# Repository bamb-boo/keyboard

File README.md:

# bamb-boo's mechanical keyboard!

This is a custom wired mechanical keyboard using a raspberry pi pico and really nice switches!! The keyboard also has a _negative_ tilt, which is better for your wrists (carpal tunnel syndrome). It uses a 16x6 matrix and has 83 keys, which is the best for my personal preference! 

It can act as an alternative to other popular keyboards like the Aula F75 or similar keyboards due to its more ergonomic and hand-friendly design!

### Features!

- Has 83 keys (~75% keyboard)

- Non-hotswappable Click Inc HP Switches (hotswappable will increase cost and design time, so kept it simple ;] )

- Runs on a Raspberry Pi Pico due to its powerful chip and the number of IO pins (26 pins)

- Has a 16x6 matrix, which is all I need for my needs (_not_ an aspiring accountant, though it'll be cool to have a larger keyboard)

- 1N4148 through-hole diodes to prevent ghosting (The matrix is a useful way of succinctly employing a limited number of IO pins for a large number of keys)

### Why I made it

To be honest, I had a faulty laptop keyboard, and wanted to get a mechanical keyboard. Creating my own keyboard >>> buying a pre-made one, so I just decided to make one on a whim! ✨

### Future scope-

I would REALLY love to make a-

- A keyboard using a touchscreen to for more efficiency (and fun, who doesn't like repeating GIFs)
- Wireless version using Pi Pico W (because you can't always stay connected to your laptop!)
- Make a larger keyboard (because larger is always equal to better!)

### Photos-

(looks kinda wonky because my laptop became incredibly slow, and it was trouble to get anything done let alone model in fusion 360.)

(just case)

(case+pcb)

(pcb)

(schematic)

### Build instructions-

1. Solder the diodes to the designated holes in the pcb, with the diodes pointing down.

2. Solder the pi pico using headers onto the pcb

3. Flash the firmware-
    plug in the usb and connect it to a laptop.
    Drop the .uf2 file 

4. Use [https://www.keyboardtester.com/tester.html](https://www.keyboardtester.com/tester.html) to test if all connections are correct- this mitigates the need to annoyingly verify if all connections are right later on

5. Solder the switches to the holes beside the diodes.

6. Clip the stabilizers onto the pcb.

7. Attach the keycaps to the switches.

8. Attach the pcb to the plate, ensuring the fit snugly.

9. Bolt the plate to the case using the screws.

10. Viola, you're done!

Finally, I heartfully thank PCBWay for their sponsorship, which allowed me to experiment and become a creator. Their quality is very high and they offer a wide range of helpful services such as PCB manufacturing, 3D-printing and CNC machining. Visit PCBWay at [PCBWay](https://www.pcbway.com)

[Bill of Materials](https://github.com/bamb-boo/keyboard/blob/main/cart/README.md) (refer to the hyperlink for the detailed bom present in the cart directory)-
| Component name    | Qty        | Bought from | Cost (usd) |
|-------------------|------------|-----------------------------------------------------------------------------------------------------------------------------------------------------------------------------------------------------------------------------------------------------------------------|------------|
| Case              | 1          | pcbway| 50       |
| Plate             |  1          | pcbway| 30       |
|PCB                | 1          | pcbway| 30         |
| Switches          | 9 packs    | [link](https://stackskb.com/store/click-inc-hp-switch-pack-of-10-pre-order/)| 17         |
| Keycaps           | 83 keycaps | [link](https://meckeys.com/shop/accessories/keyboard-accessories/keycaps/colour-pbt-keycaps/)| about 11   |
| M2 nuts and bolts | 8          | Local vendor| 1          |
| Raspbeery pi pico | 1          | [link](https://quartzcomponents.com/products/raspberry-pi-pico?variant=37945289801912&country=IN&currency=INR&utm_medium=product_sync&utm_source=google&utm_content=sag_organic&utm_campaign=sag_organic&srsltid=AfmBOooph4yAOKlaXOlzuqV4wVWYXD59shyxalMg0NoKKp0ef7S1frVsyPs) | 3.5        |
| Stabilizers       | 5          | [link](https://www.genesispc.in/products/durock-plate-mount-stabilizers-6-25u-4x2u-black?variant=43129560924213)| 4          |
| Diodes            |83         | [link](https://www.ktron.in/product/diode-1n4148-th/?srsltid=AfmBOoqAQ2ie58oqGB9lnuLERS_E0bK5uivKzd28IHgtJRiMNgbBmKTvdes)| 0.6        |
|Total              |           |                 |148  |

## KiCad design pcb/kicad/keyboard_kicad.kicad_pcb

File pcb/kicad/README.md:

This folder contains the kicad files for the PCB.

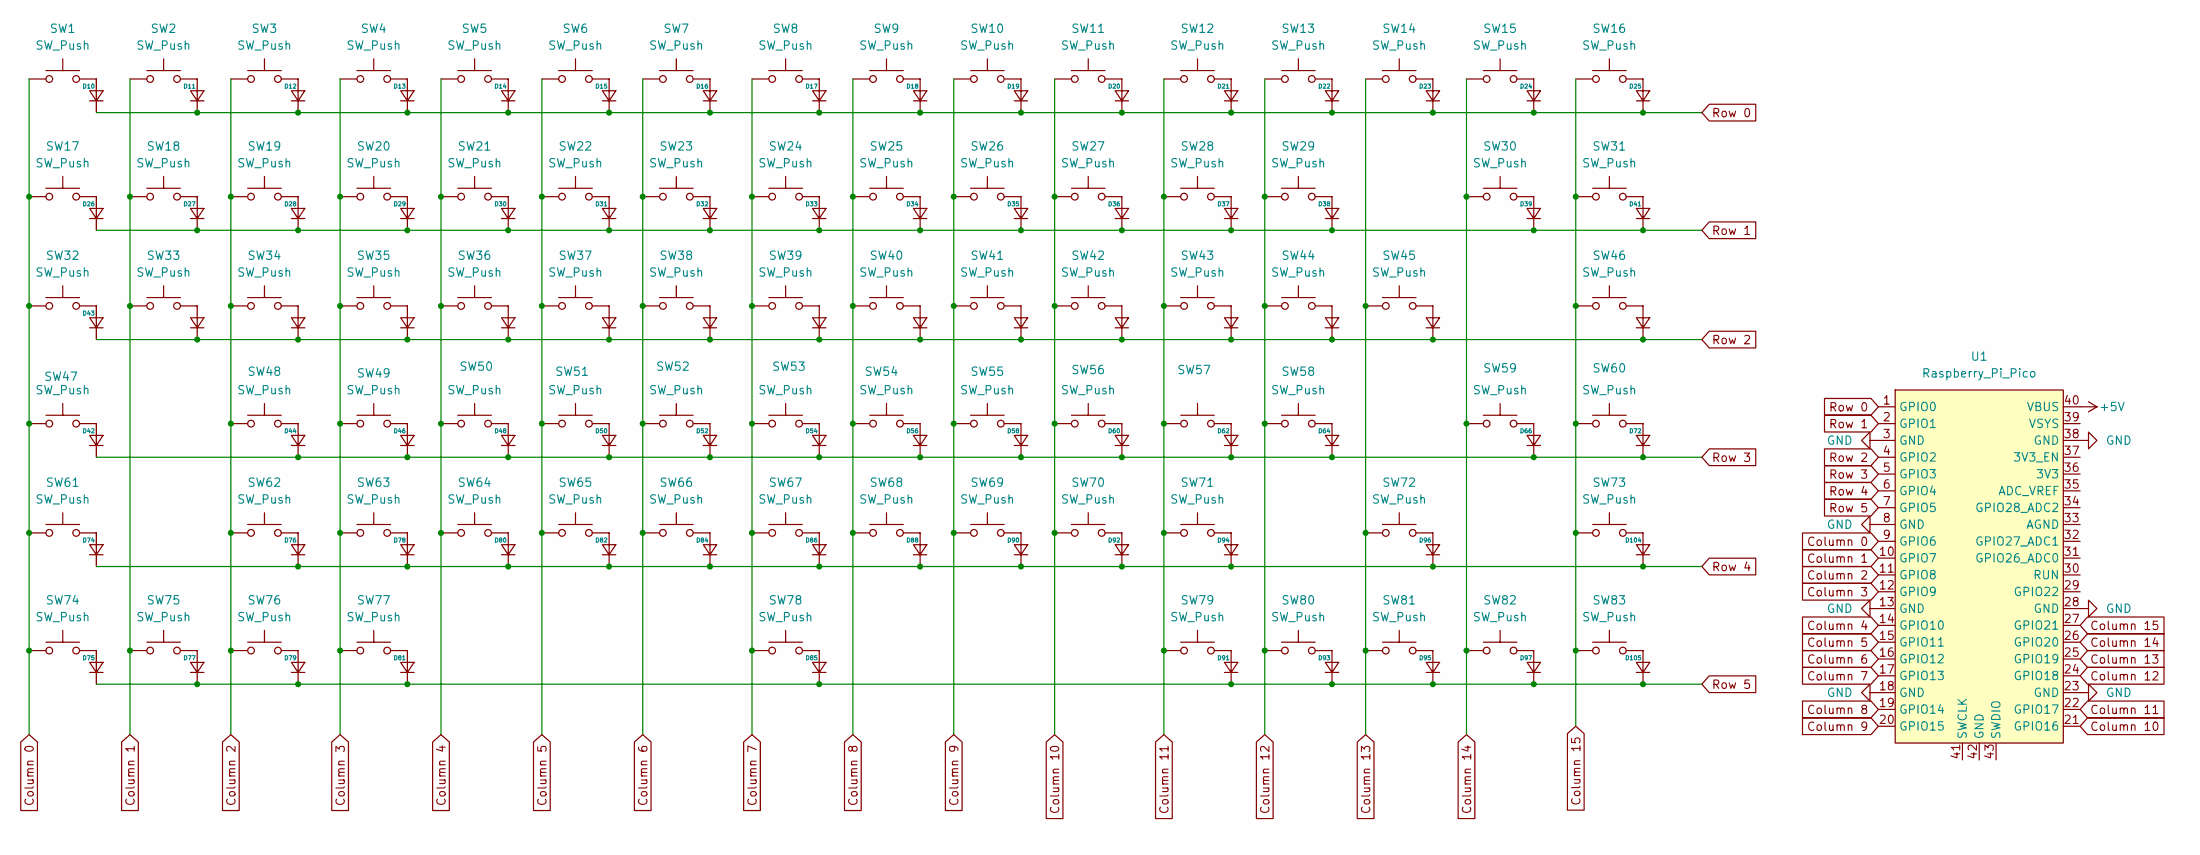
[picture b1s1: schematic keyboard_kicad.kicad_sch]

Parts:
D10, D11, D12, D13, D14, D15, D16, D17, D18, D19, D20, D21, D22, D23, D24, D25, D26, D27, D28, D29, D30, D31, D32, D33, D34, D35, D36, D37, D38, D39, D41, D42, D43, D44, D45, D46, D47, D48, D49, D50, D51, D52, D53, D54, D55, D56, D57, D58, D59, D60, D61, D62, D63, D64, D65, D66, D67, D69, D72, D73, D74, D75, D76, D77, D78, D79, D80, D81, D82, D84, D85, D86, D88, D90, D91, D92, D93, D94, D95, D96, D97, D104, D105: D_DO-35_SOD27_P3.81mm_Vertical_KathodeUp
SW1, SW2, SW3, SW4, SW5, SW6, SW7, SW8, SW9, SW10, SW11, SW12, SW13, SW14, SW15, SW16, SW17, SW18, SW19, SW20, SW21, SW22, SW23, SW24, SW25, SW26, SW27, SW28, SW29, SW31, SW33, SW34, SW35, SW36, SW37, SW38, SW39, SW40, SW41, SW42, SW43, SW44, SW46, SW48, SW49, SW50, SW51, SW52, SW53, SW54, SW55, SW56, SW57, SW58, SW60, SW62, SW63, SW64, SW65, SW66, SW67, SW68, SW69, SW70, SW71, SW73, SW79, SW80, SW81, SW82, SW83: SW_Push; MX_PCB_1.00u
SW30: SW_Push; MX_PCB_2.00u
SW32, SW45: SW_Push; MX_PCB_1.50u
SW47: SW_Push; MX_PCB_1.75u
SW59, SW61: SW_Push; MX_PCB_2.25u
SW72: SW_Push; MX_PCB_2.75u
SW74, SW75, SW76, SW77: SW_Push; MX_PCB_1.25u
SW78: SW_Push; Stabilizer_Cherry_MX_6.25u
U1: Raspberry_Pi_Pico

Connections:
+5V: U1.40 (VBUS)
Column 0: SW1.1, SW17.1, SW32.1, SW47.1, SW61.1, SW74.1, U1.9 (GPIO6)
Column 1: SW2.1, SW18.1, SW33.1, SW75.1, U1.10 (GPIO7)
Column 2: SW3.1, SW19.1, SW34.1, SW48.1, SW62.1, SW76.1, U1.11 (GPIO8)
Column 3: SW4.1, SW20.1, SW35.1, SW49.1, SW63.1, SW77.1, U1.12 (GPIO9)
Column 4: SW5.1, SW21.1, SW36.1, SW50.1, SW64.1, U1.14 (GPIO10)
Column 5: SW6.1, SW22.1, SW37.1, SW51.1, SW65.1, U1.15 (GPIO11)
Column 6: SW7.1, SW23.1, SW38.1, SW52.1, SW66.1, U1.16 (GPIO12)
Column 7: SW8.1, SW24.1, SW39.1, SW53.1, SW67.1, SW78.1, U1.17 (GPIO13)
Column 8: SW9.1, SW25.1, SW40.1, SW54.1, SW68.1, U1.19 (GPIO14)
Column 9: SW10.1, SW26.1, SW41.1, SW55.1, SW69.1, U1.20 (GPIO15)
Column 10: SW11.1, SW27.1, SW42.1, SW56.1, SW70.1, U1.21 (GPIO16)
Column 11: SW12.1, SW28.1, SW43.1, SW57.1, SW71.1, SW79.1, U1.22 (GPIO17)
Column 12: SW13.1, SW29.1, SW44.1, SW58.1, SW80.1, U1.24 (GPIO18)
Column 13: SW14.1, SW45.1, SW72.1, SW81.1, U1.25 (GPIO19)
Column 14: SW15.1, SW30.1, SW59.1, SW82.1, U1.26 (GPIO20)
Column 15: SW16.1, SW31.1, SW46.1, SW60.1, SW73.1, SW83.1, U1.27 (GPIO21)
GND: U1.3 (GND), U1.8 (GND), U1.13 (GND), U1.18 (GND), U1.23 (GND), U1.28 (GND), U1.38 (GND)
unnamed: D10.2 (A), SW1.2
unnamed: D11.2 (A), SW2.2
unnamed: D12.2 (A), SW3.2
unnamed: D13.2 (A), SW4.2
unnamed: D14.2 (A), SW5.2
unnamed: D15.2 (A), SW6.2
unnamed: D16.2 (A), SW7.2
unnamed: D17.2 (A), SW8.2
unnamed: D18.2 (A), SW9.2
unnamed: D19.2 (A), SW10.2
unnamed: D20.2 (A), SW11.2
unnamed: D21.2 (A), SW12.2
unnamed: D22.2 (A), SW13.2
unnamed: D23.2 (A), SW14.2
unnamed: D24.2 (A), SW15.2
unnamed: D25.2 (A), SW16.2
unnamed: D26.2 (A), SW17.2
unnamed: D27.2 (A), SW18.2
unnamed: D28.2 (A), SW19.2
unnamed: D29.2 (A), SW20.2
unnamed: D30.2 (A), SW21.2
unnamed: D31.2 (A), SW22.2
unnamed: D32.2 (A), SW23.2
unnamed: D33.2 (A), SW24.2
unnamed: D34.2 (A), SW25.2
unnamed: D35.2 (A), SW26.2
unnamed: D36.2 (A), SW27.2
unnamed: D37.2 (A), SW28.2
unnamed: D38.2 (A), SW29.2
unnamed: D39.2 (A), SW30.2
unnamed: D41.2 (A), SW31.2
unnamed: D42.2 (A), SW47.2
unnamed: D43.2 (A), SW32.2
unnamed: D44.2 (A), SW48.2
unnamed: D45.2 (A), SW33.2
unnamed: D46.2 (A), SW49.2
unnamed: D47.2 (A), SW34.2
unnamed: D48.2 (A), SW50.2
unnamed: D49.2 (A), SW35.2
unnamed: D50.2 (A), SW51.2
unnamed: D51.2 (A), SW36.2
unnamed: D52.2 (A), SW52.2
unnamed: D53.2 (A), SW37.2
unnamed: D54.2 (A), SW53.2
unnamed: D55.2 (A), SW38.2
unnamed: D56.2 (A), SW54.2
unnamed: D57.2 (A), SW39.2
unnamed: D58.2 (A), SW55.2
unnamed: D59.2 (A), SW40.2
unnamed: D60.2 (A), SW56.2
unnamed: D61.2 (A), SW41.2
unnamed: D62.2 (A), SW57.2
unnamed: D63.2 (A), SW42.2
unnamed: D64.2 (A), SW58.2
unnamed: D65.2 (A), SW43.2
unnamed: D66.2 (A), SW59.2
unnamed: D67.2 (A), SW44.2
unnamed: D69.2 (A), SW45.2
unnamed: D72.2 (A), SW60.2
unnamed: D73.2 (A), SW46.2
unnamed: D74.2 (A), SW61.2
unnamed: D75.2 (A), SW74.2
unnamed: D76.2 (A), SW62.2
unnamed: D77.2 (A), SW75.2
unnamed: D78.2 (A), SW63.2
unnamed: D79.2 (A), SW76.2
unnamed: D80.2 (A), SW64.2
unnamed: D81.2 (A), SW77.2
unnamed: D82.2 (A), SW65.2
unnamed: D84.2 (A), SW66.2
unnamed: D85.2 (A), SW78.2
unnamed: D86.2 (A), SW67.2
unnamed: D88.2 (A), SW68.2
unnamed: D90.2 (A), SW69.2
unnamed: D91.2 (A), SW79.2
unnamed: D92.2 (A), SW70.2
unnamed: D93.2 (A), SW80.2
unnamed: D94.2 (A), SW71.2
unnamed: D95.2 (A), SW81.2
unnamed: D96.2 (A), SW72.2
unnamed: D97.2 (A), SW82.2
unnamed: D104.2 (A), SW73.2
unnamed: D105.2 (A), SW83.2
Row 0: D10.1 (K), D11.1 (K), D12.1 (K), D13.1 (K), D14.1 (K), D15.1 (K), D16.1 (K), D17.1 (K), D18.1 (K), D19.1 (K), D20.1 (K), D21.1 (K), D22.1 (K), D23.1 (K), D24.1 (K), D25.1 (K), U1.1 (GPIO0)
Row 1: D26.1 (K), D27.1 (K), D28.1 (K), D29.1 (K), D30.1 (K), D31.1 (K), D32.1 (K), D33.1 (K), D34.1 (K), D35.1 (K), D36.1 (K), D37.1 (K), D38.1 (K), D39.1 (K), D41.1 (K), U1.2 (GPIO1)
Row 2: D43.1 (K), D45.1 (K), D47.1 (K), D49.1 (K), D51.1 (K), D53.1 (K), D55.1 (K), D57.1 (K), D59.1 (K), D61.1 (K), D63.1 (K), D65.1 (K), D67.1 (K), D69.1 (K), D73.1 (K), U1.4 (GPIO2)
Row 3: D42.1 (K), D44.1 (K), D46.1 (K), D48.1 (K), D50.1 (K), D52.1 (K), D54.1 (K), D56.1 (K), D58.1 (K), D60.1 (K), D62.1 (K), D64.1 (K), D66.1 (K), D72.1 (K), U1.5 (GPIO3)
Row 4: D74.1 (K), D76.1 (K), D78.1 (K), D80.1 (K), D82.1 (K), D84.1 (K), D86.1 (K), D88.1 (K), D90.1 (K), D92.1 (K), D94.1 (K), D96.1 (K), D104.1 (K), U1.6 (GPIO4)
Row 5: D75.1 (K), D77.1 (K), D79.1 (K), D81.1 (K), D85.1 (K), D91.1 (K), D93.1 (K), D95.1 (K), D97.1 (K), D105.1 (K), U1.7 (GPIO5)

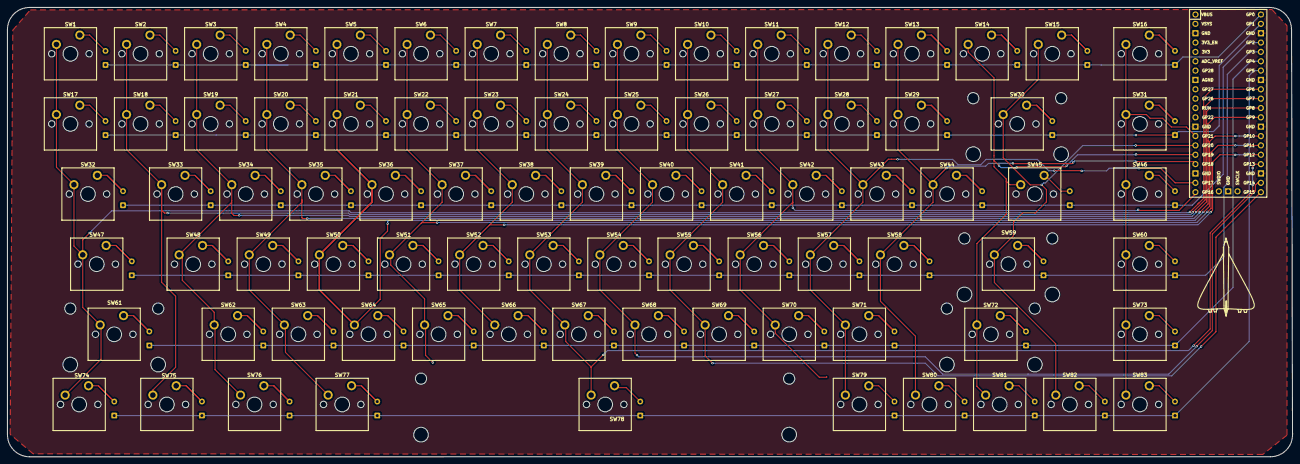
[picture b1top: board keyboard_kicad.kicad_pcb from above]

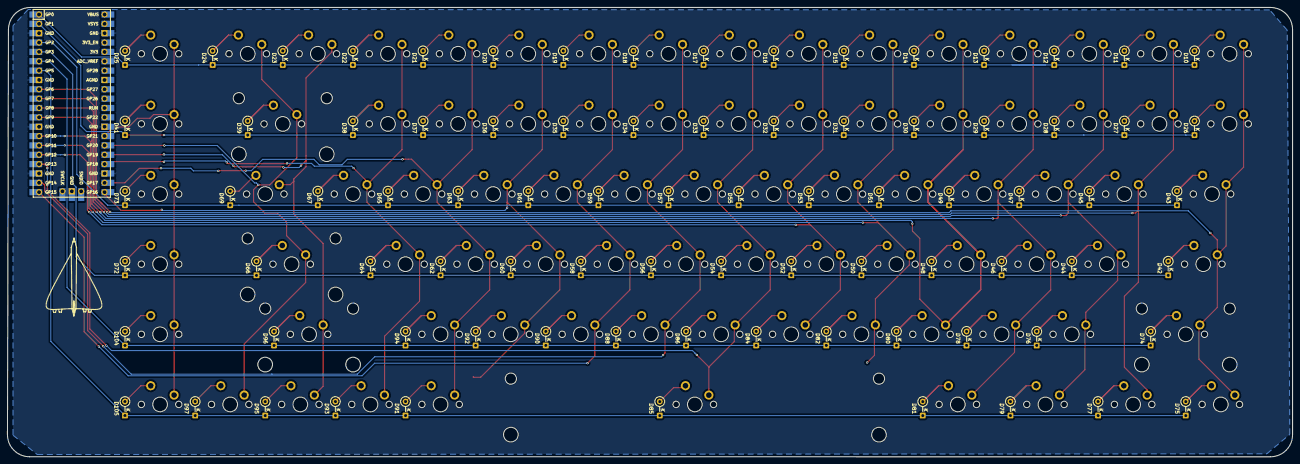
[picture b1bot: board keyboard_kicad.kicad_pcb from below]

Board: 2 copper layers, 349.1 x 122.0 mm, 167 parts (84 on the bottom side), 106 nets.

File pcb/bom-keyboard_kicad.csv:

"Id";"Designator";"Footprint";"Quantity";"Designation";"Supplier and ref";
1;"SW83,SW71,SW4,SW54,SW41,SW18,SW38,SW44,SW82,SW46,SW9,SW15,SW81,SW58,SW43,SW6,SW22,SW60,SW37,SW52,SW36,SW50,SW33,SW2,SW35,SW20,SW56,SW7,SW62,SW31,SW14,SW26,SW66,SW10,SW1,SW39,SW80,SW70,SW8,SW53,SW73,SW5,SW27,SW42,SW68,SW51,SW3,SW57,SW25,SW23,SW79,SW29,SW17,SW13,SW24,SW12,SW28,SW65,SW21,SW69,SW63,SW67,SW34,SW16,SW19,SW55,SW48,SW40,SW64,SW49,SW11";"MX_PCB_1.00u";71;"SW_Push";;;
2;"SW75,SW74,SW77,SW76";"MX_PCB_1.25u";4;"SW_Push";;;
3;"SW45,SW32";"MX_PCB_1.50u";2;"SW_Push";;;
4;"SW59,SW61";"MX_PCB_2.25u";2;"SW_Push";;;
5;"SW30";"MX_PCB_2.00u";1;"SW_Push";;;
6;"SW78";"Stabilizer_Cherry_MX_6.25u";1;"SW_Push";;;
7;"SW47";"MX_PCB_1.75u";1;"SW_Push";;;
8;"SW72";"MX_PCB_2.75u";1;"SW_Push";;;
9;"D52,D35,D94,D61,D90,D29,D97,D47,D23,D51,D63,D43,D26,D22,D38,D105,D67,D30,D17,D15,D19,D10,D69,D34,D82,D33,D39,D50,D66,D45,D77,D79,D59,D53,D64,D80,D104,D37,D73,D78,D36,D92,D65,D13,D88,D24,D20,D32,D11,D60,D44,D72,D42,D14,D12,D41,D95,D49,D16,D86,D93,D54,D27,D58,D18,D74,D31,D96,D85,D81,D28,D84,D75,D21,D56,D91,D55,D25,D57,D62,D48,D76,D46";"D_DO-35_SOD27_P3.81mm_Vertical_KathodeUp";83;"~";;;
10;"U1";"Raspberry_Pi_Pico";1;"Raspberry_Pi_Pico";;;

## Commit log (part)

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2026-05-07 added README.md
2026-06-27 Rename keyboard_kicad-all-pos.csv to cpl-keyboard_kicad-all-pos.csv
2026-06-27 Rename keyboard_kicad.csv to bom-keyboard_kicad.csv
